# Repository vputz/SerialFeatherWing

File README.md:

This is a Serial DB9 featherwing based on ppelleti's fantastic and
helpful [FeatherWing-template-KiCad][1] project.  The intent is to
make it possible to drive old DB9-serial devices from the comfort
of a modern FeatherWing board, and to eliminate the need for the old
Orbotron boards.

## License

This repository is licensed under [the same terms as the KiCad
libraries][9], which is the [CC-BY-SA 4.0][10] license, with an
exception that says that electronic designs based on this repository
are not bound by the attribution and share-alike conditions.

[1]: http:github.com/ppelleti/FeatherWing-template-KiCad
[9]: https://forum.kicad.info/t/kicad-library-licensing/7856
[10]: https://creativecommons.org/licenses/by-sa/4.0/legalcode

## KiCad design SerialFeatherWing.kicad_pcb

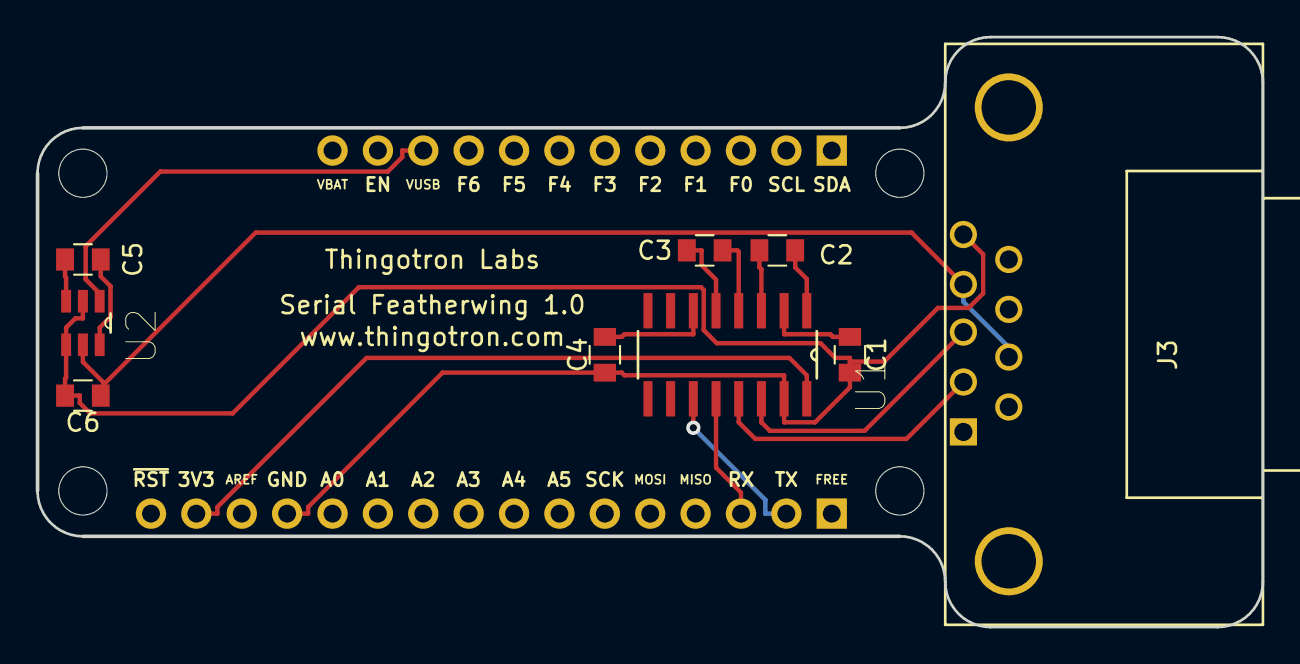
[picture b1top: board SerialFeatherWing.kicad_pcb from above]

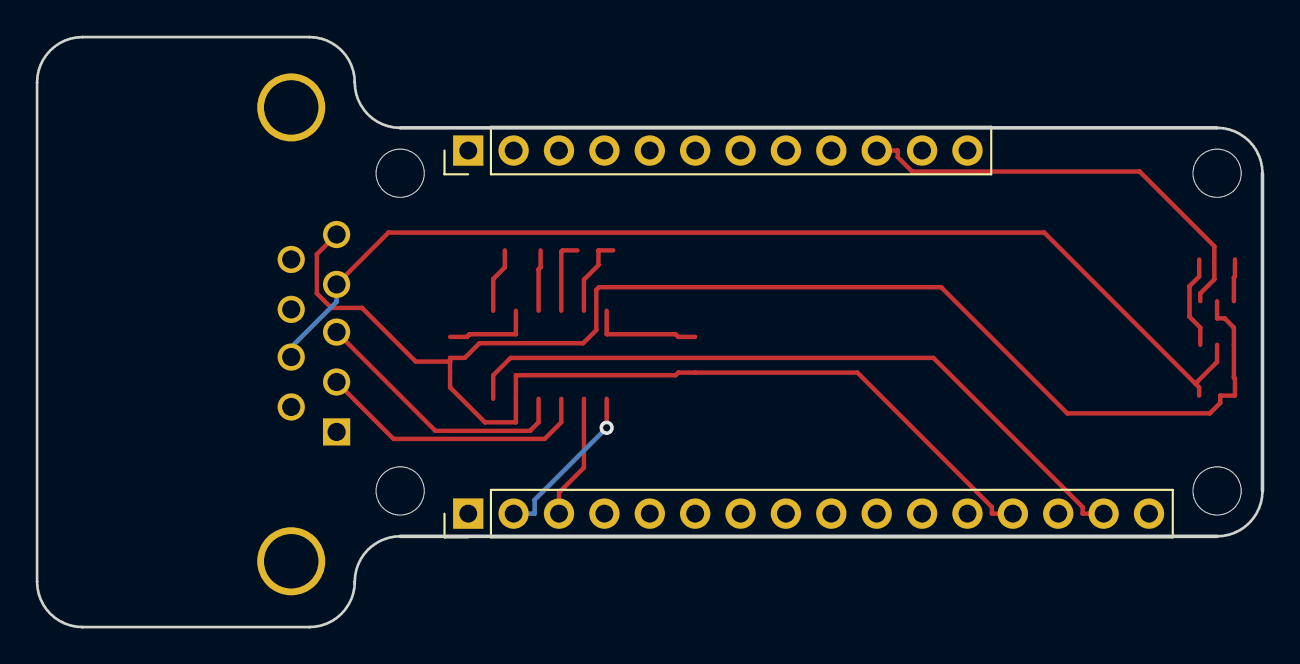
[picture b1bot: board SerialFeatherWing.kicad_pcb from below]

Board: 2 copper layers, 68.6 x 33.0 mm, 14 parts (2 on the bottom side), 16 nets.

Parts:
C1, C2, C3, C4: 0.1uf; C_0805
C5, C6: 10uf; C_0805
H1, H2, H4: MountingHole_2.7mm_M2.5
J1: feather long; PinHeader_1x16_P2.54mm_Vertical
J2: feather short; PinHeader_1x12_P2.54mm_Vertical
J3: DB9_Male; DB9MC
U1: ST3232CDR; SOIC127P600X175-16N
U2: TC1240AECHTR; SOT95P280X145-6N

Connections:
+3V3: J1.15, U1.16
+10V: C6.1, J3.4, J3.7, U2.5
GND: C1.2, C4.2, C6.2, J1.13, J3.5, U1.15, U2.2, U2.4
unnamed: C1.1, U1.2
unnamed: C2.1, U1.1
unnamed: C2.2, U1.3
unnamed: C3.1, U1.4
unnamed: C3.2, U1.5
unnamed: C4.1, U1.6
unnamed: C5.1, U2.6
unnamed: C5.2, U2.3
unnamed: J3.2, U1.13
unnamed: J3.3, U1.14
RX0: J1.3, U1.12
TX0: J1.2, U1.11
VUSB: J2.10, U2.1

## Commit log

2020-01-12 Initial Import
2020-02-24 current revision; this works very well
2020-03-10 tried connector on end--tested good
